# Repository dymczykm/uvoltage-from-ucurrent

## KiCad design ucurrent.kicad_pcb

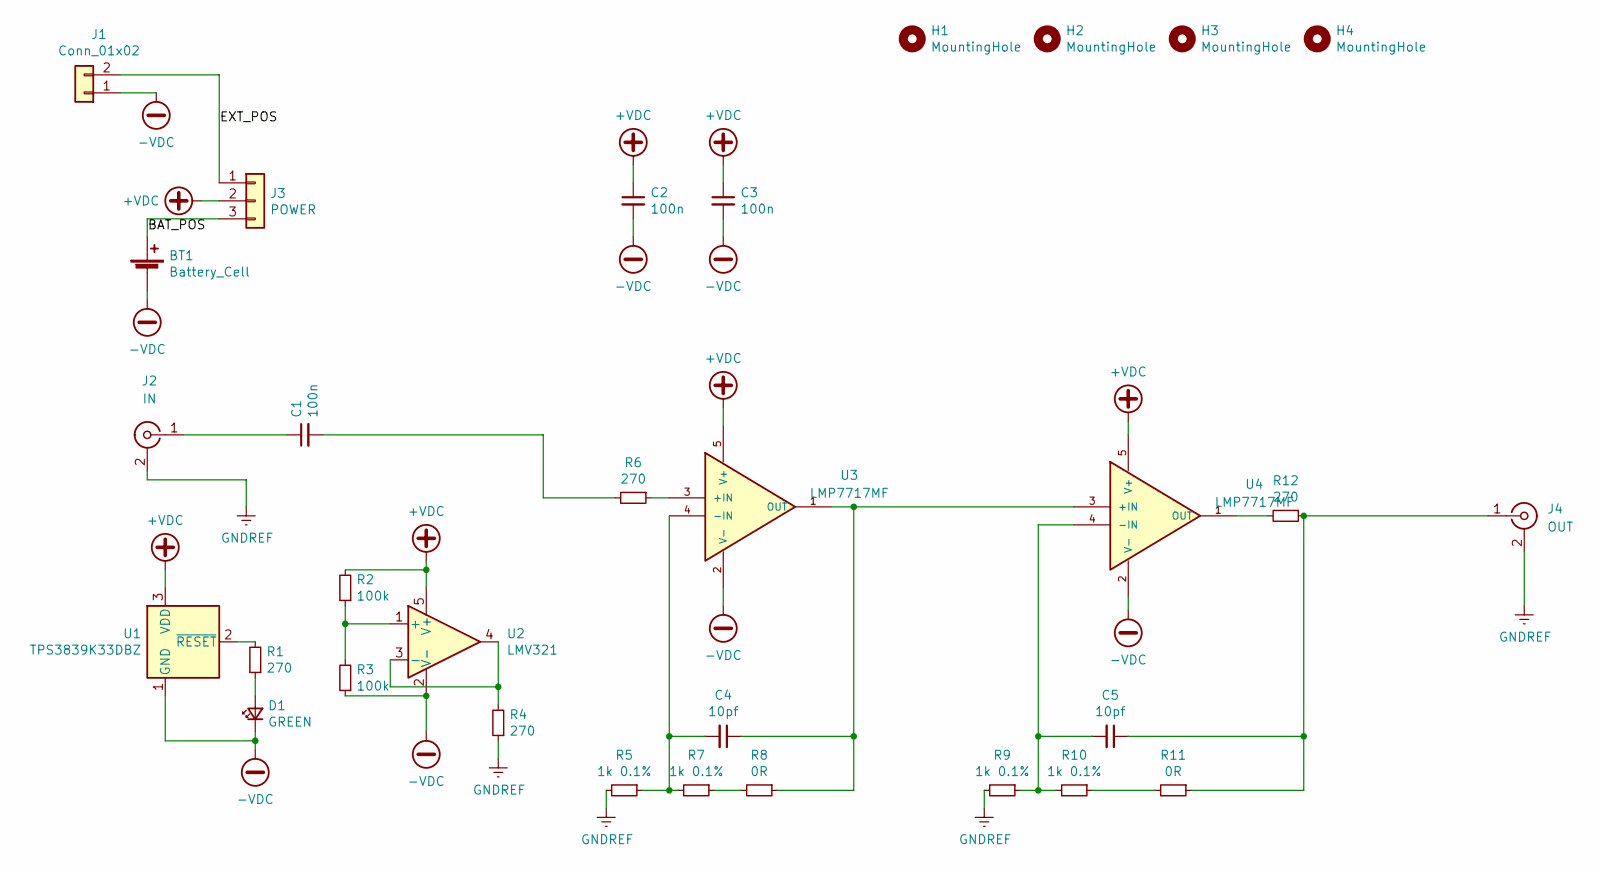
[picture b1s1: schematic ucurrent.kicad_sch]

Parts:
BT1: Battery_Cell; BatteryHolder_Keystone_1060_1x2032; LCSC DO NOT POPULATE
C1, C2, C3: 100n; C_0805_2012Metric_Pad1.18x1.45mm_HandSolder; LCSC C49678
C4, C5: 10pf; C_0805_2012Metric_Pad1.18x1.45mm_HandSolder; LCSC C107110
D1: GREEN; LED_0805_2012Metric_Pad1.15x1.40mm_HandSolder; LCSC DO NOT POPULATE
H1, H2, H3, H4: MountingHole; MountingHole_2.2mm_M2; LCSC DO NOT POPULATE
J1: Conn_01x02; PinHeader_1x02_P2.54mm_Vertical; LCSC DO NOT POPULATE
J2: IN; BNC_TEConnectivity_1478204_Vertical; LCSC DO NOT POPULATE
J3: POWER; PinHeader_1x03_P2.54mm_Vertical; LCSC DO NOT POPULATE
J4: OUT; BNC_TEConnectivity_1478204_Vertical; LCSC DO NOT POPULATE
R1, R4, R6, R12: 270; R_0603_1608Metric_Pad0.98x0.95mm_HandSolder; LCSC C22966
R2, R3: 100k; R_0603_1608Metric_Pad0.98x0.95mm_HandSolder; LCSC C25803
R5, R7, R9, R10: 1k 0.1%; R_0805_2012Metric_Pad1.20x1.40mm_HandSolder; LCSC C17513
R8, R11: 0R; R_0805_2012Metric_Pad1.20x1.40mm_HandSolder; LCSC C17477
U1: TPS3839K33DBZ; SOT-23; LCSC C96333
U2: LMV321; SOT-23-5_HandSoldering; LCSC C7972
U3, U4: LMP7717MF; SOT95P280X145-5N; LCSC C202279

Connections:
+VDC: C2.1, C3.1, J3.2, R2.2, U1.3 (VDD), U2.5 (V+), U3.5 (V+), U4.5 (V+)
-VDC: BT1.2 (-), C2.2, C3.2, D1.1 (K), J1.1, R3.1, U1.1 (GND), U2.2 (V-), U3.2 (V-), U4.2 (V-)
/BAT_POS: BT1.1 (+), J3.3
/EXT_POS: J1.2, J3.1
GNDREF: J2.2 (Ext), J4.2 (Ext), R4.1, R5.2, R9.2
unnamed: C1.1, J2.1 (In)
unnamed: C1.2, R6.2
unnamed: C4.1, R8.1, U3.1 (OUT), U4.3 (+IN)
unnamed: C4.2, R5.1, R7.2, U3.4 (-IN)
unnamed: C5.2, R9.1, R10.2, U4.4 (-IN)
unnamed: D1.2 (A), R1.1
unnamed: C5.1, J4.1 (In), R11.1, R12.1
unnamed: R1.2, U1.2 (~RESET)
unnamed: R2.1, R3.2, U2.1 (+)
unnamed: R4.2, U2.3 (-), U2.4
unnamed: R6.1, U3.3 (+IN)
unnamed: R7.1, R8.2
unnamed: R10.1, R11.2
unnamed: R12.2, U4.1 (OUT)

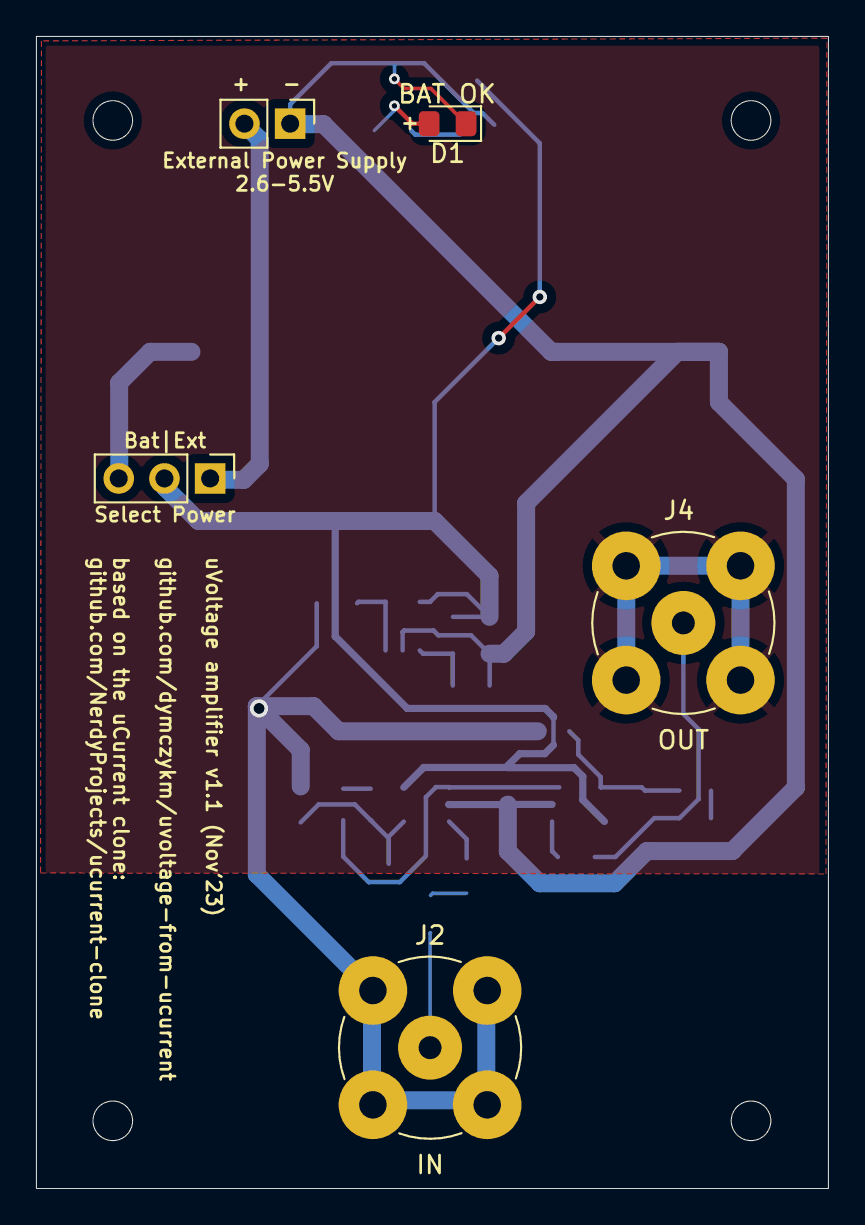
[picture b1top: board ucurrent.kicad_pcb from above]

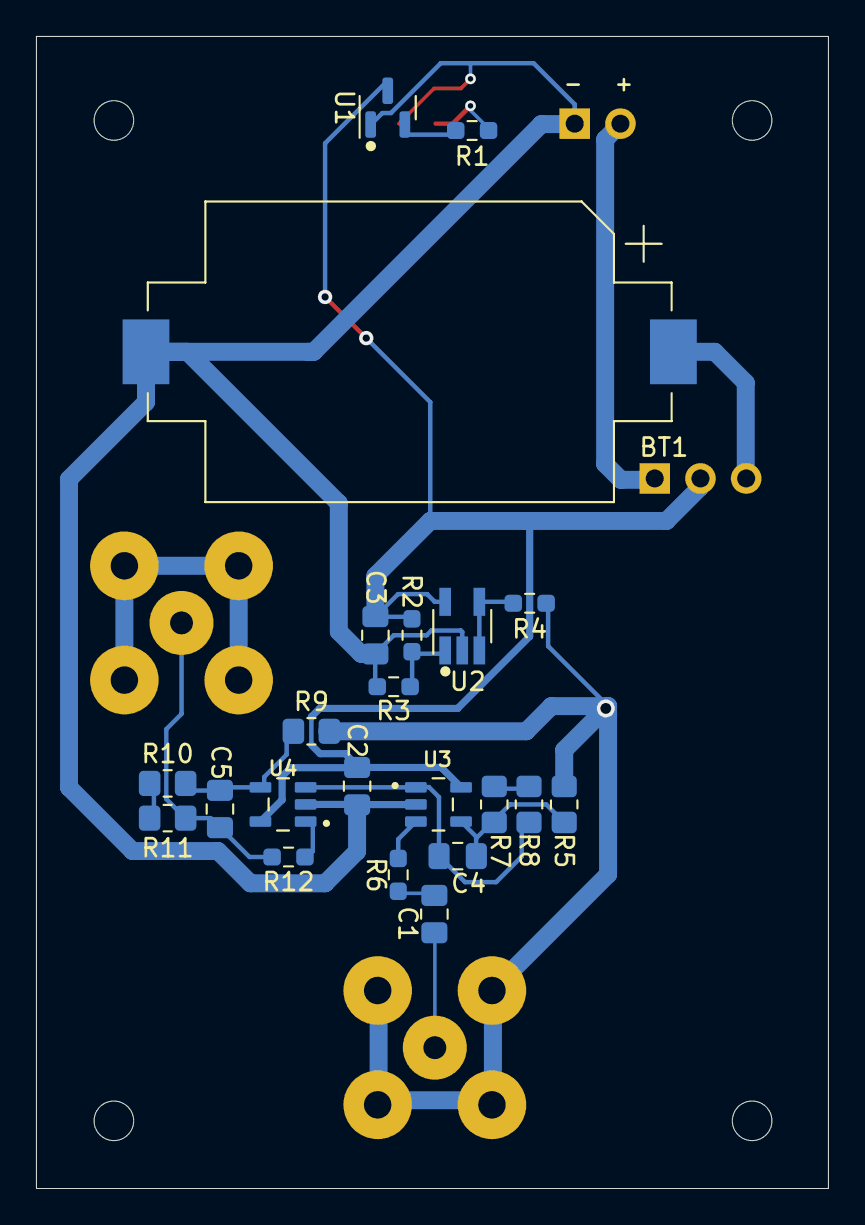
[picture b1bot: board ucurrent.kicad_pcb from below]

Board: 2 copper layers, 44.0 x 64.0 mm, 31 parts (26 on the bottom side), 19 nets.

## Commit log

2023-09-21 Redid the schematic for voltage measurement, added JLCPCB component references.
2023-11-04 Updated to LMP7717, v1.1.
